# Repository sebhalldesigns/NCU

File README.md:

# NCU
NCU (Network Control Unit)

## Main Connector Pinout

GND
12V

CAN0_L
CAN0_H
CAN1_L
CAN1_H

ETH_TXP
ETH_TXM
ETH_RXP
ETH_RXM

USB_VBUS
USB_DP
USB_DM
GND

AN_5V
AN_GND
AIN_0
AIN_1
AIN_2
AIN_3
AIN_4
AIN_5
AIN_6
AIN_7

HSD_0
HSD_1
HSD_2
HSD_3

LSD_0
LSD_1
LSD_2
LSD_3

TOTAL:
30

## Sheets

Root/
    CONN_A - OK
    CONN_B - OK
    PWR/ - OK
        PWR_LV_5V - OK
        PWR_3V3 - OK
        PWR_A5V - OK
        PWR_MUX - OK
    PHY_CAN/ - OK
        CAN_BUS (x2) - OK
    PHY_ETH - OK
    DRIVES/ - OK
        LSD (x2) - OK
        HSD (x2) - OK
    INPUTS/ - OK
        INPUT_5V (x4) - OK
        INPUT_20V (x5) - OK
    GPIO/ - OK
        INPUT_3V3 (x4) - OK
    CARD_SD - OK
    CARD_SIM - OK
    MOD_WLAN - BAD
    MOD_PCIE - BAD
    MCU - BAD

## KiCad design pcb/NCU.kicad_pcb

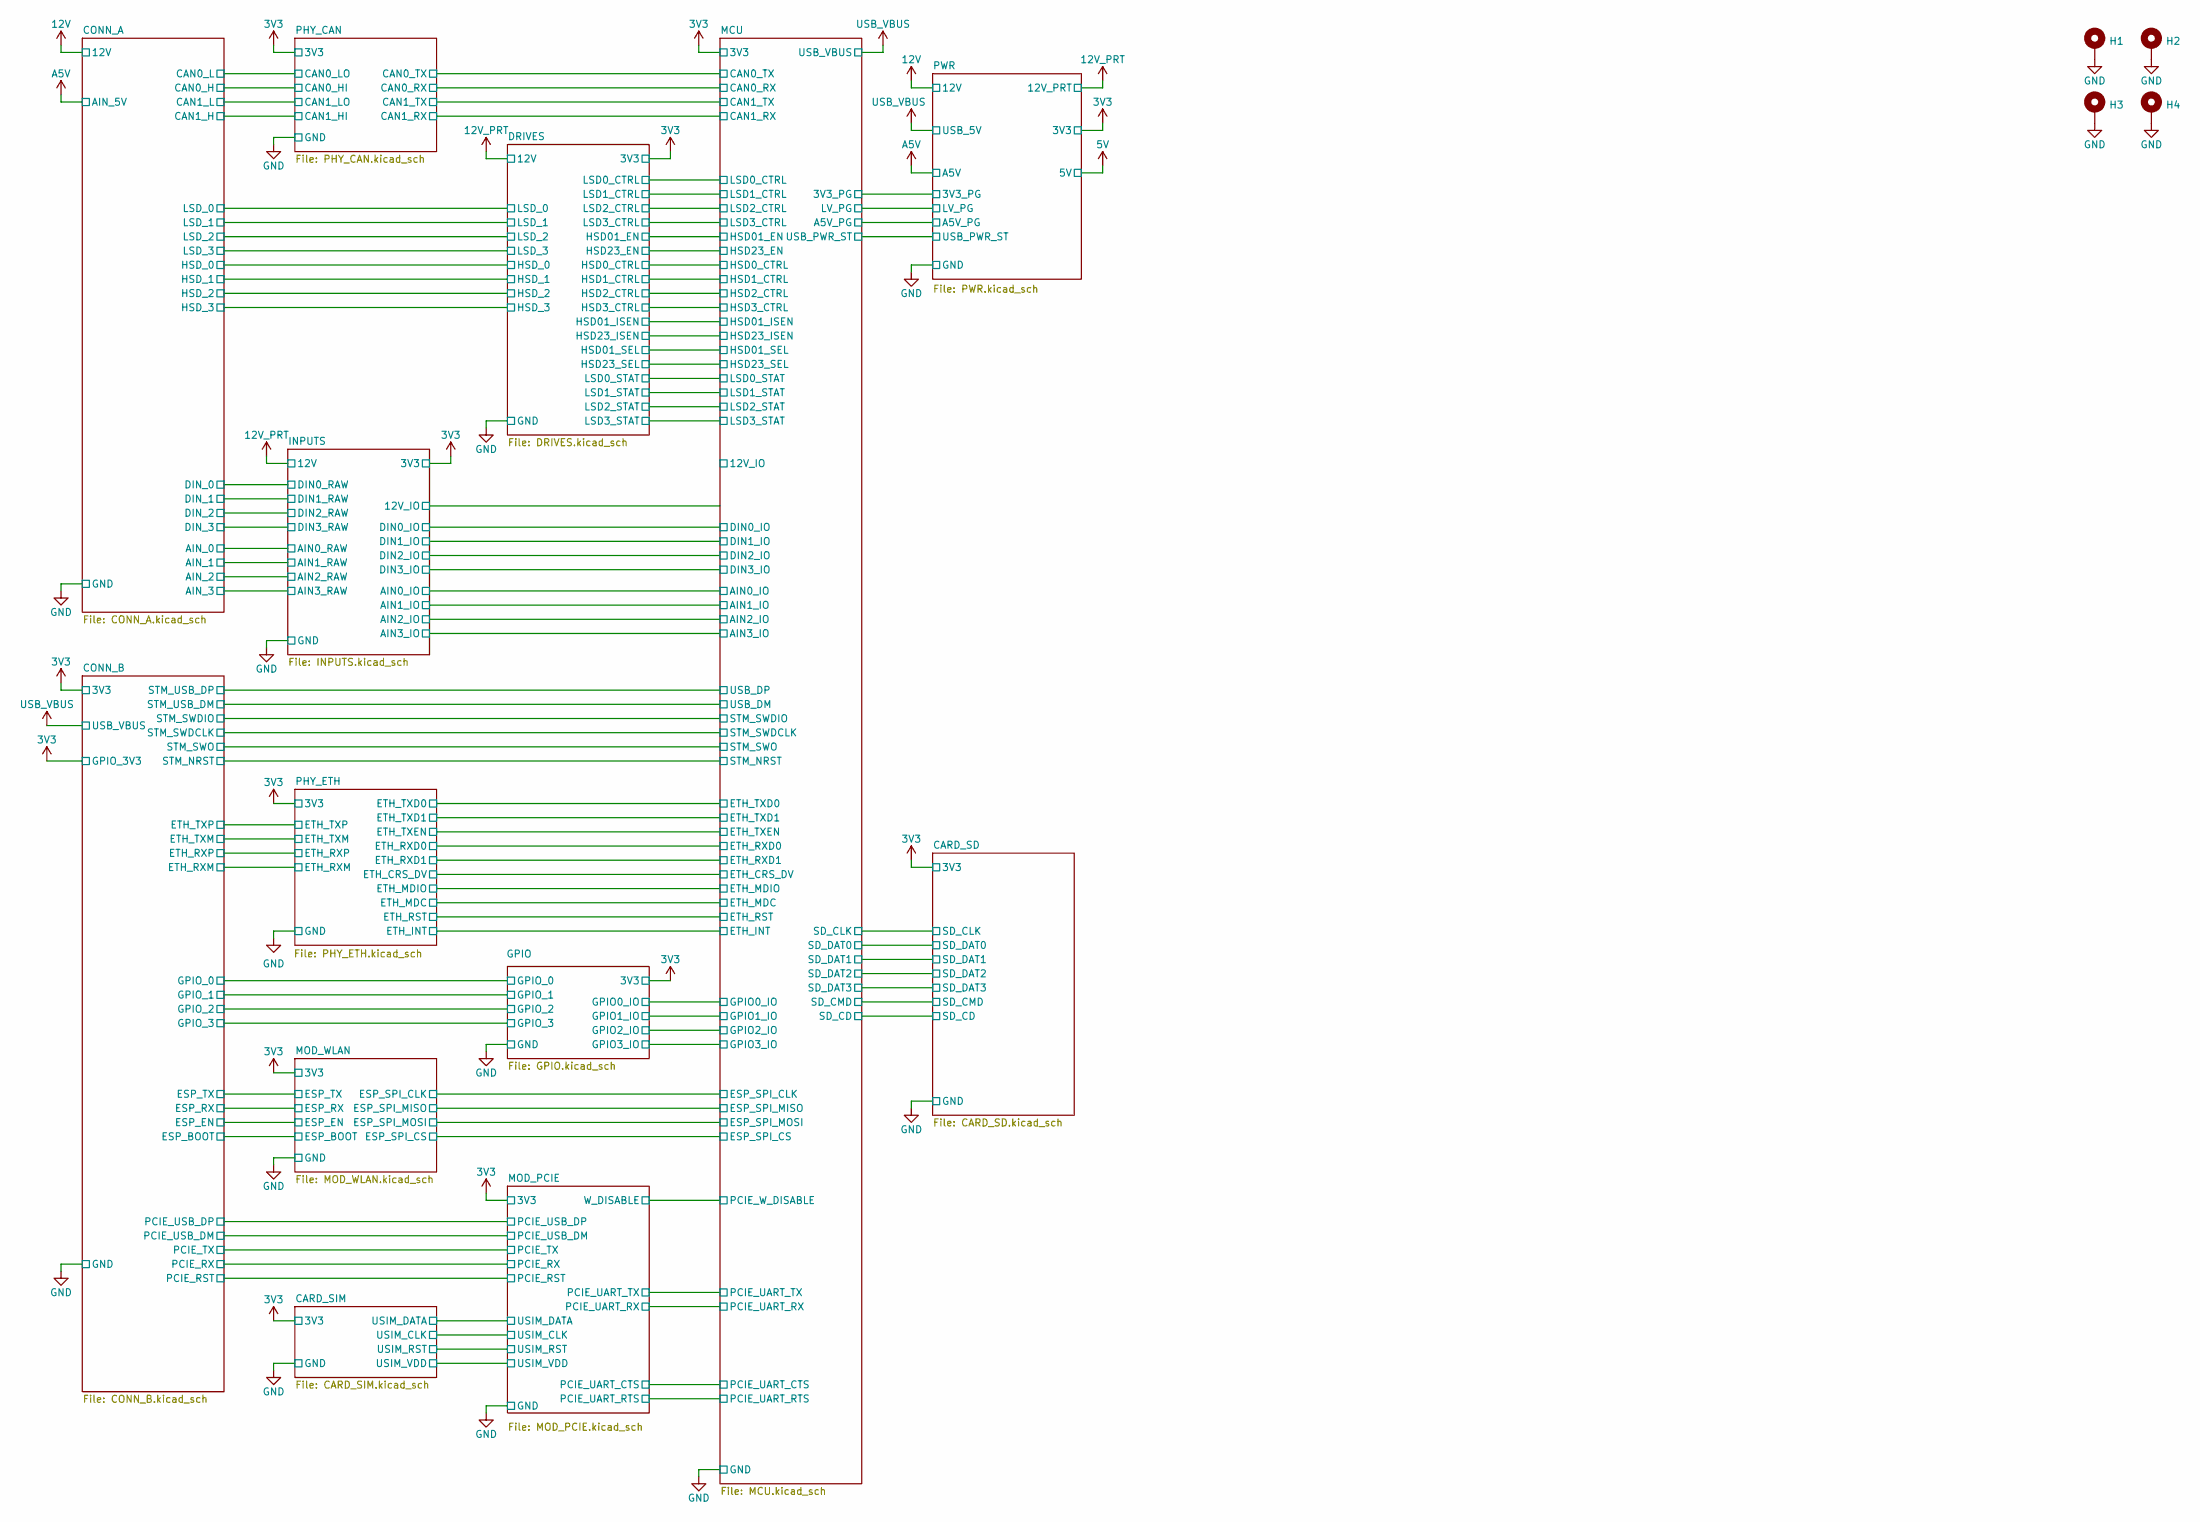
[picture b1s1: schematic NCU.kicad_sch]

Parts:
H1, H2, H3, H4: MountingHole; MountingHole_3.2mm_M3_Pad

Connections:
GND: H1.1, H2.1, H3.1, H4.1; also elsewhere on the board

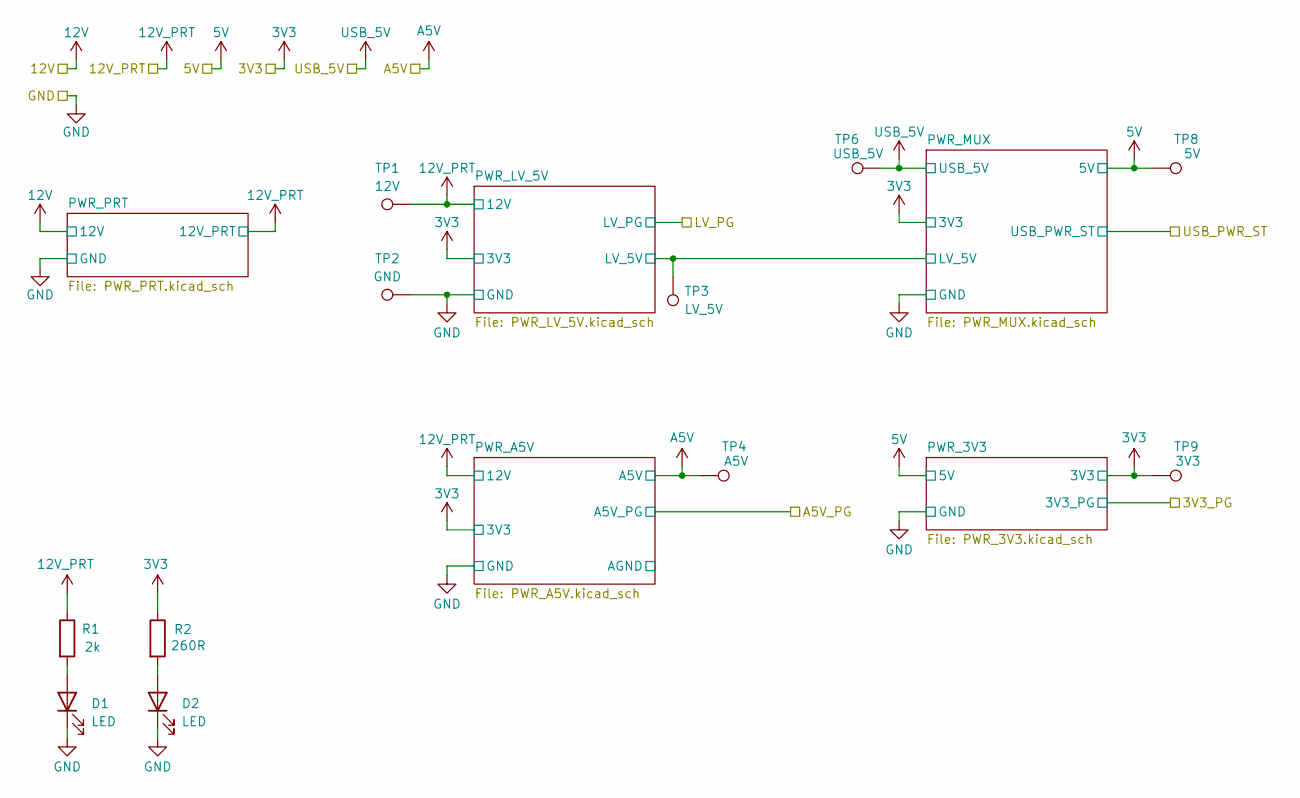
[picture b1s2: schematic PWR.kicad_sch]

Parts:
D1, D2: LED; LED_0603_1608Metric_Pad1.05x0.95mm_HandSolder
R1: 2k; R_0603_1608Metric_Pad0.98x0.95mm_HandSolder
R2: 260R; R_0603_1608Metric_Pad0.98x0.95mm_HandSolder
TP1: 12V; TestPoint_THTPad_D2.0mm_Drill1.0mm
TP2: GND; TestPoint_THTPad_D2.0mm_Drill1.0mm
TP3: LV_5V; TestPoint_THTPad_D2.0mm_Drill1.0mm
TP4: A5V; TestPoint_THTPad_D2.0mm_Drill1.0mm
TP6: USB_5V; TestPoint_THTPad_D2.0mm_Drill1.0mm
TP8: 5V; TestPoint_THTPad_D2.0mm_Drill1.0mm
TP9: 3V3; TestPoint_THTPad_D2.0mm_Drill1.0mm

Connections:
3V3: R2.1, TP9.1; also elsewhere on the board
5V: TP8.1; also elsewhere on the board
12V_PRT: R1.1, TP1.1; also elsewhere on the board
A5V: TP4.1; also elsewhere on the board
GND: D1.1 (K), D2.1 (K), TP2.1; also elsewhere on the board
LV_5V: TP3.1; also elsewhere on the board
unnamed: D1.2 (A), R1.2
unnamed: D2.2 (A), R2.2
USB_VBUS: TP6.1; also elsewhere on the board

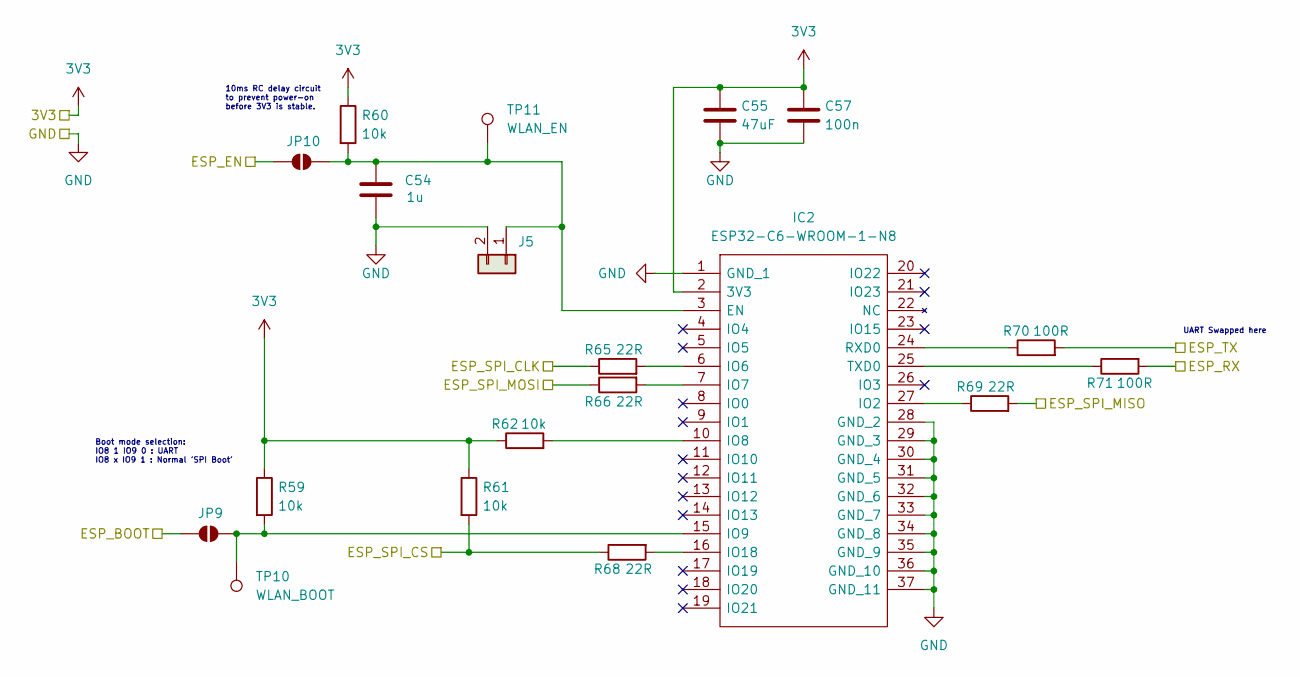
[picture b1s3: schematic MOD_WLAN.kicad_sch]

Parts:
C54: 1u; C_0603_1608Metric_Pad1.08x0.95mm_HandSolder
C55: 47uF; C_0603_1608Metric_Pad1.08x0.95mm_HandSolder
C57: 100n; C_0603_1608Metric_Pad1.08x0.95mm_HandSolder
IC2: ESP32-C6-WROOM-1-N8; ESP32C6WROOM1N8; Mouser Part Number 356-ESP32C6WROOM1N8
J5: Conn_01x02; PinHeader_1x02_P2.54mm_Vertical
JP9, JP10: SolderJumper_2_Open; SolderJumper-2_P1.3mm_Open_RoundedPad1.0x1.5mm
R59, R60, R61, R62: 10k; R_0603_1608Metric_Pad0.98x0.95mm_HandSolder
R65, R66, R68, R69: 22R; R_0603_1608Metric_Pad0.98x0.95mm_HandSolder
R70, R71: 100R; R_0603_1608Metric_Pad0.98x0.95mm_HandSolder
TP10: WLAN_BOOT; TestPoint_THTPad_D2.0mm_Drill1.0mm
TP11: WLAN_EN; TestPoint_THTPad_D2.0mm_Drill1.0mm

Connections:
3V3: C55.1, C57.1, IC2.2 (3V3), R59.1, R60.1, R61.1, R62.1; also elsewhere on the board
/CONN_B/ESP_BOOT: JP9.1 (A); also elsewhere on the board
/CONN_B/ESP_EN: JP10.1 (A); also elsewhere on the board
/CONN_B/ESP_RX: R71.2; also elsewhere on the board
/CONN_B/ESP_TX: R70.2; also elsewhere on the board
/MCU/ESP_SPI_CLK: R65.1; also elsewhere on the board
/MCU/ESP_SPI_CS: R61.2, R68.1; also elsewhere on the board
/MCU/ESP_SPI_MISO: R69.2; also elsewhere on the board
/MCU/ESP_SPI_MOSI: R66.1; also elsewhere on the board
GND: C54.2, C55.2, C57.2, IC2.1 (GND_1), IC2.28 (GND_2), IC2.29 (GND_3), IC2.30 (GND_4), IC2.31 (GND_5), IC2.32 (GND_6), IC2.33 (GND_7), IC2.34 (GND_8), IC2.35 (GND_9), IC2.36 (GND_10), IC2.37 (GND_11), J5.2; also elsewhere on the board
unnamed: C54.1, IC2.3 (EN), J5.1, JP10.2 (B), R60.2, TP11.1
unnamed: IC2.27 (IO2), R69.1
unnamed: IC2.6 (IO6), R65.2
unnamed: IC2.7 (IO7), R66.2
unnamed: IC2.10 (IO8), R62.2
unnamed: IC2.15 (IO9), JP9.2 (B), R59.2, TP10.1
unnamed: IC2.16 (IO18), R68.2
unnamed: IC2.24 (RXD0), R70.1
unnamed: IC2.25 (TXD0), R71.1

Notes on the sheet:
Boot mode selection: IO8 1 IO9 0 : UART IO8 x IO9 1 : Normal 'SPI Boot'
10ms RC delay circuit to prevent power-on before 3V3 is stable.
UART Swapped here

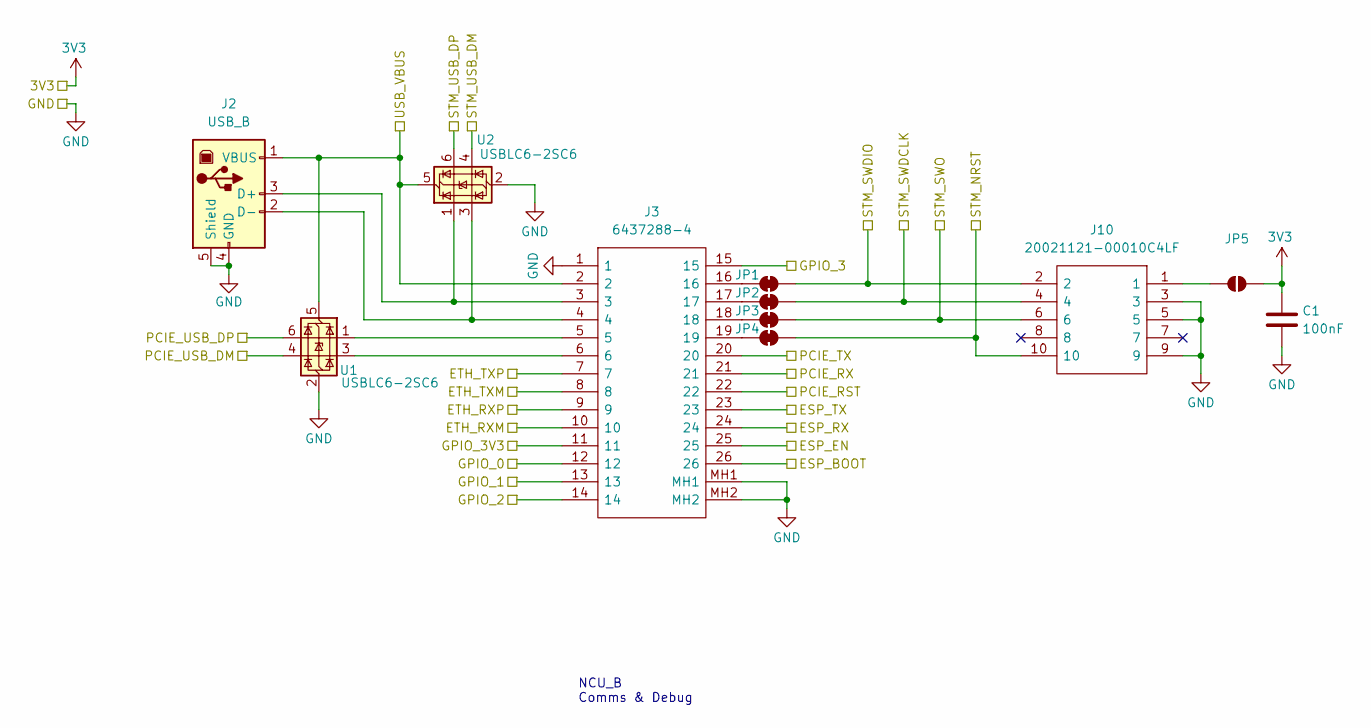
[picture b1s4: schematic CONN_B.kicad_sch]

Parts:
C1: 100nF; C_0603_1608Metric_Pad1.08x0.95mm_HandSolder
J2: USB_B; USB_B_OST_USB-B1HSxx_Horizontal
J3: 6437288-4; 64372884; Mouser Part Number 571-6437288-4
J10: 20021121-00010C4LF; 2002112100010C4LF; Mouser Part Number 649-202112100010C4LF
JP1, JP2, JP3, JP4: SolderJumper_2_Bridged; SolderJumper-2_P1.3mm_Bridged_RoundedPad1.0x1.5mm
JP5: SolderJumper_2_Open; SolderJumper-2_P1.3mm_Open_RoundedPad1.0x1.5mm
U1, U2: USBLC6-2SC6; SOT-23-6

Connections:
3V3: C1.1, J3.11, JP5.2 (B); also elsewhere on the board
/CONN_B/ESP_BOOT: J3.26; also elsewhere on the board
/CONN_B/ESP_EN: J3.25; also elsewhere on the board
/CONN_B/ESP_RX: J3.24; also elsewhere on the board
/CONN_B/ESP_TX: J3.23; also elsewhere on the board
/CONN_B/ETH_RXM: J3.10; also elsewhere on the board
/CONN_B/ETH_RXP: J3.9; also elsewhere on the board
/CONN_B/ETH_TXM: J3.8; also elsewhere on the board
/CONN_B/ETH_TXP: J3.7; also elsewhere on the board
/CONN_B/GPIO_0: J3.12; also elsewhere on the board
/CONN_B/GPIO_1: J3.13; also elsewhere on the board
/CONN_B/GPIO_2: J3.14; also elsewhere on the board
/CONN_B/GPIO_3: J3.15; also elsewhere on the board
/CONN_B/PCIE_RST: J3.22; also elsewhere on the board
/CONN_B/PCIE_RX: J3.21; also elsewhere on the board
/CONN_B/PCIE_TX: J3.20; also elsewhere on the board
/CONN_B/PCIE_USB_DM: U1.4 (I/O2); also elsewhere on the board
/CONN_B/PCIE_USB_DP: U1.6 (I/O1); also elsewhere on the board
/CONN_B/STM_SWDCLK: J10.4, JP2.2 (B); also elsewhere on the board
/CONN_B/STM_SWDIO: J10.2, JP1.2 (B); also elsewhere on the board
/CONN_B/STM_SWO: J10.6, JP3.2 (B); also elsewhere on the board
/CONN_B/STM_USB_DM: U2.4 (I/O2); also elsewhere on the board
/CONN_B/STM_USB_DP: U2.6 (I/O1); also elsewhere on the board
/MCU/STM_NRST: J10.10, JP4.2 (B); also elsewhere on the board
GND: C1.2, J2.4 (GND), J2.5 (Shield), J3.1, J3.MH1, J3.MH2, J10.3, J10.5, J10.9, U1.2 (GND), U2.2 (GND); also elsewhere on the board
unnamed: J2.3 (D+), J3.3, U2.1 (I/O1)
unnamed: J2.2 (D-), J3.4, U2.3 (I/O2)
unnamed: J3.5, U1.1 (I/O1)
unnamed: J3.6, U1.3 (I/O2)
unnamed: J3.16, JP1.1 (A)
unnamed: J3.17, JP2.1 (A)
unnamed: J3.18, JP3.1 (A)
unnamed: J3.19, JP4.1 (A)
unnamed: J10.1, JP5.1 (A)
USB_VBUS: J2.1 (VBUS), J3.2, U1.5 (VBUS), U2.5 (VBUS); also elsewhere on the board

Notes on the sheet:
NCU_B Comms & Debug

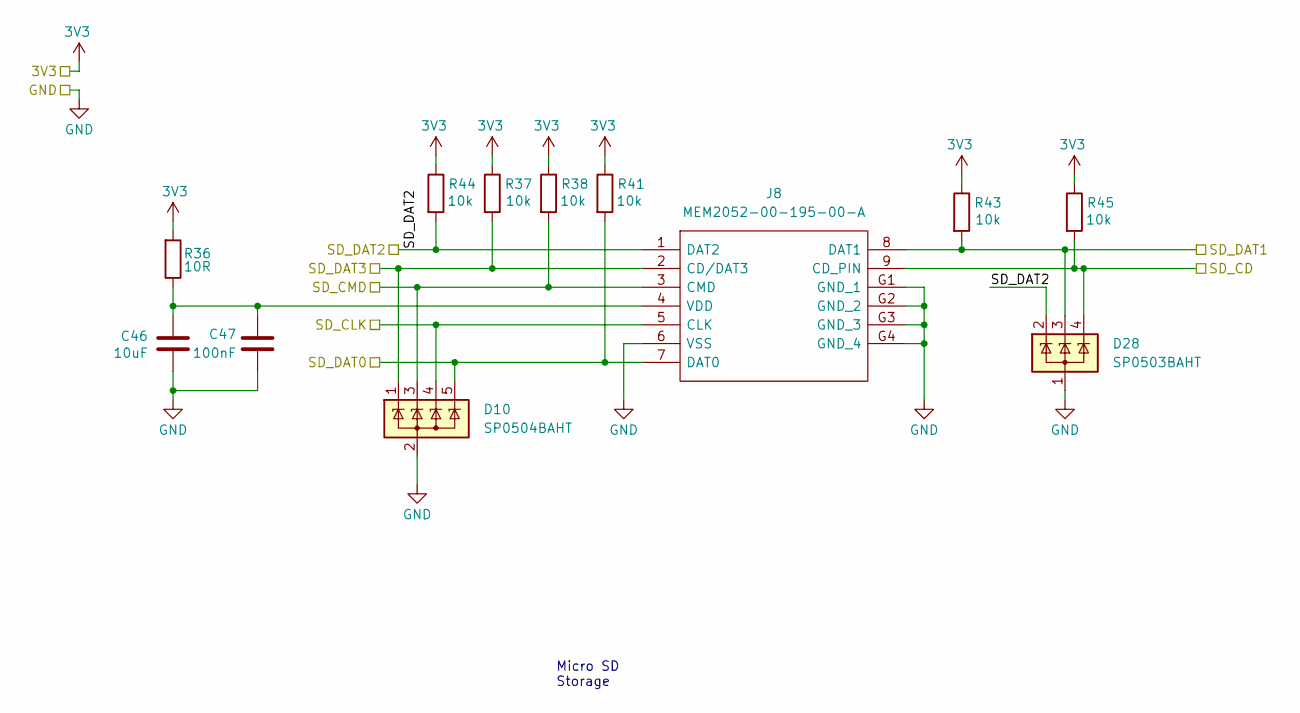
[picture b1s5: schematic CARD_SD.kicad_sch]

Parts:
C46: 10uF; C_0603_1608Metric_Pad1.08x0.95mm_HandSolder
C47: 100nF; C_0603_1608Metric_Pad1.08x0.95mm_HandSolder
D10: SP0504BAHT; SOT-23-5
D28: SP0503BAHT; SOT-143
J8: MEM2052-00-195-00-A; MEM20520019500A; Mouser Part Number 640-MEM20520019500A
R36: 10R; R_0603_1608Metric_Pad0.98x0.95mm_HandSolder
R37, R38, R41, R43, R44, R45: 10k; R_0603_1608Metric_Pad0.98x0.95mm_HandSolder

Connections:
3V3: R36.2, R37.1, R38.1, R41.1, R43.1, R44.1, R45.1; also elsewhere on the board
/CARD_SD/SD_CD: D28.4 (K), J8.9 (CD_PIN), R45.2; also elsewhere on the board
/CARD_SD/SD_CLK: D10.4 (K), J8.5 (CLK); also elsewhere on the board
/CARD_SD/SD_CMD: D10.3 (K), J8.3 (CMD), R38.2; also elsewhere on the board
/CARD_SD/SD_DAT0: D10.5 (K), J8.7 (DAT0), R41.2; also elsewhere on the board
/CARD_SD/SD_DAT1: D28.3 (K), J8.8 (DAT1), R43.2; also elsewhere on the board
/CARD_SD/SD_DAT2: D28.2 (K), J8.1 (DAT2), R44.2; also elsewhere on the board
/CARD_SD/SD_DAT3: D10.1 (K), J8.2 (CD/DAT3), R37.2; also elsewhere on the board
GND: C46.2, C47.2, D10.2 (A), D28.1 (A), J8.6 (VSS), J8.G1 (GND_1), J8.G2 (GND_2), J8.G3 (GND_3), J8.G4 (GND_4); also elsewhere on the board
unnamed: C46.1, C47.1, J8.4 (VDD), R36.1

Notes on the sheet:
Micro SD Storage

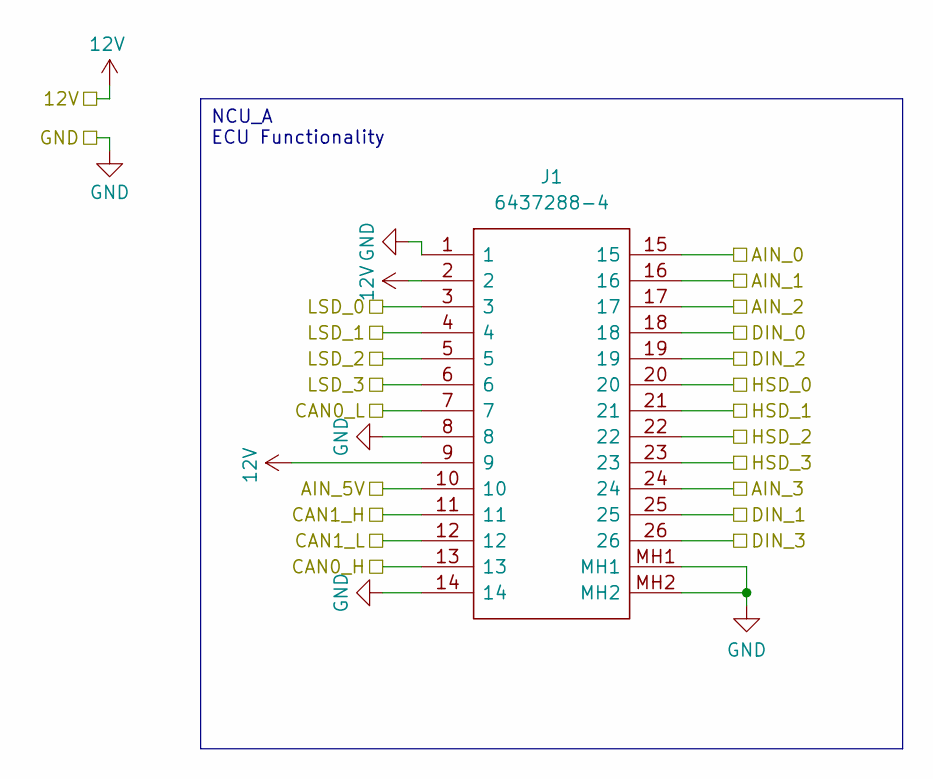
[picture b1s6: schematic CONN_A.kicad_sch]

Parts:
J1: 6437288-4; 64372884; Mouser Part Number 571-6437288-4

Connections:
12V: J1.2, J1.9; also elsewhere on the board
/CONN_A/AIN_0: J1.15; also elsewhere on the board
/CONN_A/AIN_1: J1.16; also elsewhere on the board
/CONN_A/AIN_2: J1.17; also elsewhere on the board
/CONN_A/AIN_3: J1.24; also elsewhere on the board
/CONN_A/CAN0_H: J1.13; also elsewhere on the board
/CONN_A/CAN0_L: J1.7; also elsewhere on the board
/CONN_A/CAN1_H: J1.11; also elsewhere on the board
/CONN_A/CAN1_L: J1.12; also elsewhere on the board
/CONN_A/DIN_0: J1.18; also elsewhere on the board
/CONN_A/DIN_1: J1.25; also elsewhere on the board
/CONN_A/DIN_2: J1.19; also elsewhere on the board
/CONN_A/DIN_3: J1.26; also elsewhere on the board
/CONN_A/HSD_0: J1.20; also elsewhere on the board
/CONN_A/HSD_1: J1.21; also elsewhere on the board
/CONN_A/HSD_2: J1.22; also elsewhere on the board
/CONN_A/HSD_3: J1.23; also elsewhere on the board
/CONN_A/LSD_0: J1.3; also elsewhere on the board
/CONN_A/LSD_1: J1.4; also elsewhere on the board
/CONN_A/LSD_2: J1.5; also elsewhere on the board
/CONN_A/LSD_3: J1.6; also elsewhere on the board
A5V: J1.10; also elsewhere on the board
GND: J1.1, J1.8, J1.14, J1.MH1, J1.MH2; also elsewhere on the board

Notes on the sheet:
NCU_A ECU Functionality

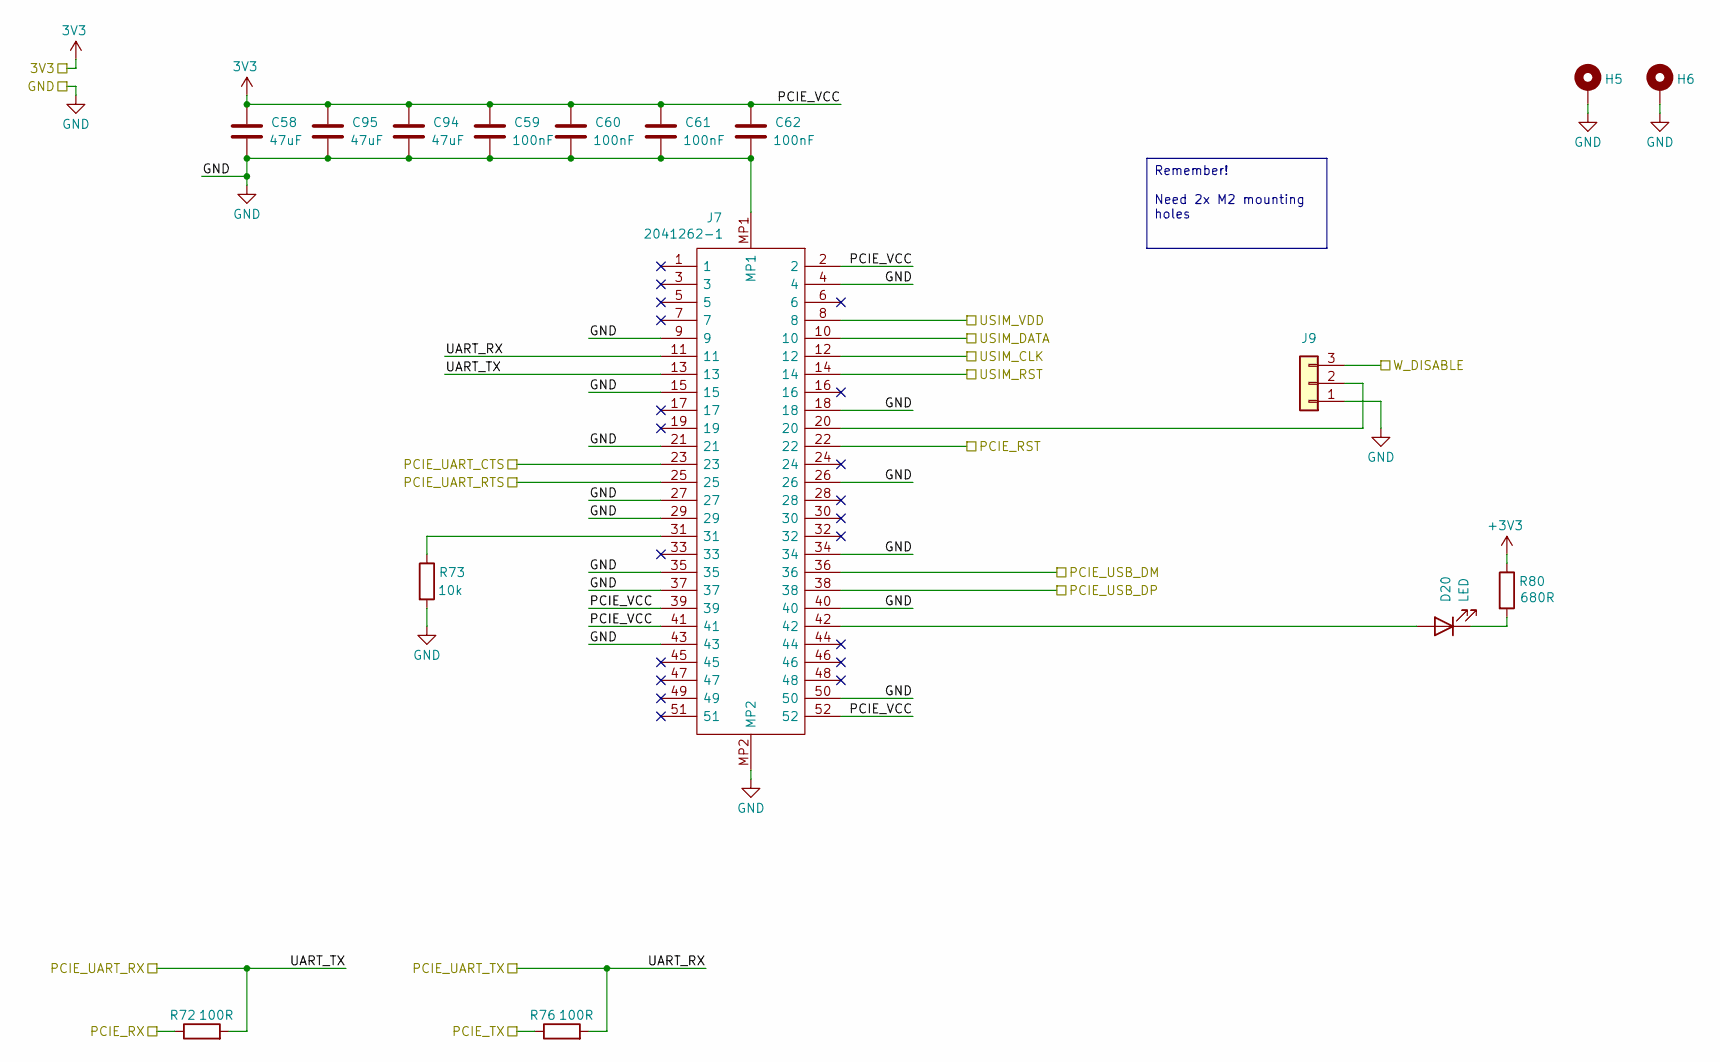
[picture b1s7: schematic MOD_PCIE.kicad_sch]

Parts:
C58, C94, C95: 47uF; C_0603_1608Metric_Pad1.08x0.95mm_HandSolder
C59, C60, C61, C62: 100nF; C_0603_1608Metric_Pad1.08x0.95mm_HandSolder
D20: LED; LED_0603_1608Metric_Pad1.05x0.95mm_HandSolder
H5, H6: MountingHole_Pad; MountingHole_2.7mm_M2.5_Pad
J7: 2041262-1; 20412621; Mouser Part Number 571-2041262-1
J9: Conn_01x03; PinHeader_1x03_P2.54mm_Vertical
R72, R76: 100R; R_0603_1608Metric_Pad0.98x0.95mm_HandSolder
R73: 10k; R_0603_1608Metric_Pad0.98x0.95mm_HandSolder
R80: 680R; R_0603_1608Metric_Pad0.98x0.95mm_HandSolder

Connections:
3V3: C58.1, C59.1, C60.1, C61.1, C62.1, C94.1, C95.1, J7.2, J7.39, J7.41, J7.52; also elsewhere on the board
+3V3: R80.1
/CARD_SIM/USIM_CLK: J7.12; also elsewhere on the board
/CARD_SIM/USIM_DATA: J7.10; also elsewhere on the board
/CARD_SIM/USIM_RST: J7.14; also elsewhere on the board
/CARD_SIM/USIM_VDD: J7.8; also elsewhere on the board
/CONN_B/PCIE_RST: J7.22; also elsewhere on the board
/CONN_B/PCIE_RX: R72.1; also elsewhere on the board
/CONN_B/PCIE_TX: R76.1; also elsewhere on the board
/CONN_B/PCIE_USB_DM: J7.36; also elsewhere on the board
/CONN_B/PCIE_USB_DP: J7.38; also elsewhere on the board
/MCU/PCIE_UART_CTS: J7.23; also elsewhere on the board
/MCU/PCIE_UART_RTS: J7.25; also elsewhere on the board
/MCU/PCIE_W_DISABLE: J9.3; also elsewhere on the board
/MOD_PCIE/UART_RX: J7.11, R76.2; also elsewhere on the board
/MOD_PCIE/UART_TX: J7.13, R72.2; also elsewhere on the board
GND: C58.2, C59.2, C60.2, C61.2, C62.2, C94.2, C95.2, H5.1, H6.1, J7.4, J7.9, J7.15, J7.18, J7.21, J7.26, J7.27, J7.29, J7.34, J7.35, J7.37, J7.40, J7.43, J7.50, J7.MP1, J7.MP2, J9.1, R73.2; also elsewhere on the board
unnamed: D20.2 (A), J7.42
unnamed: D20.1 (K), R80.2
unnamed: J7.31, R73.1
unnamed: J7.20, J9.2

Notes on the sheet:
Remember! Need 2x M2 mounting holes

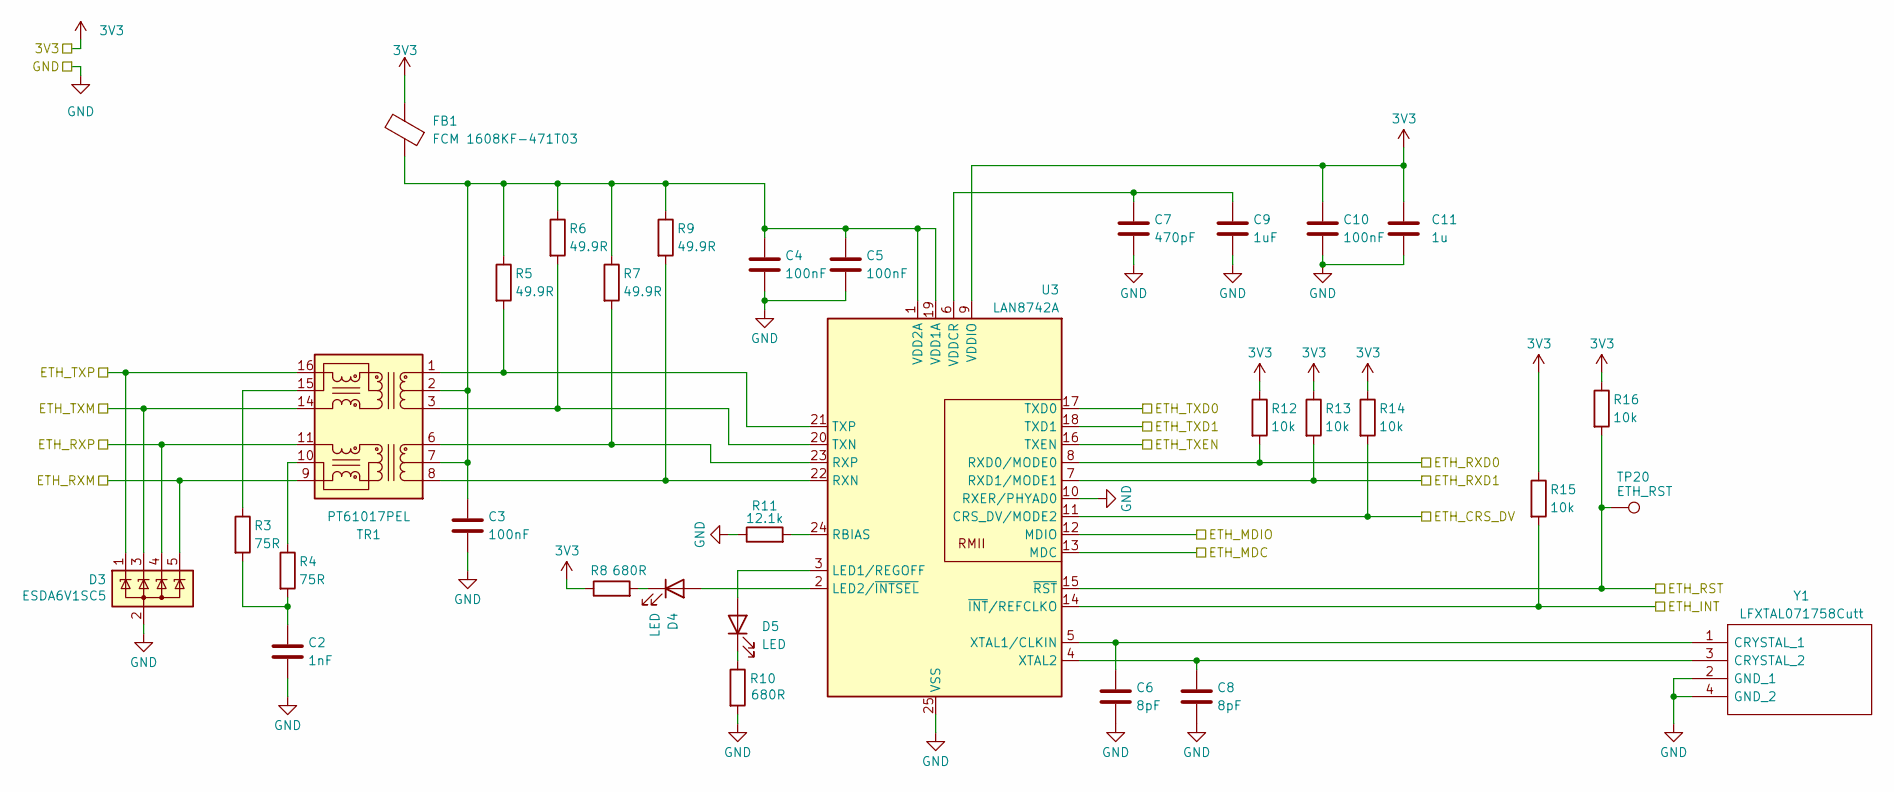
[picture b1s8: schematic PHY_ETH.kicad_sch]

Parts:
C2: 1nF; C_0603_1608Metric_Pad1.08x0.95mm_HandSolder
C3, C4, C5, C10: 100nF; C_0603_1608Metric_Pad1.08x0.95mm_HandSolder
C6, C8: 8pF; C_0603_1608Metric_Pad1.08x0.95mm_HandSolder
C7: 470pF; C_0603_1608Metric_Pad1.08x0.95mm_HandSolder
C9: 1uF; C_0603_1608Metric_Pad1.08x0.95mm_HandSolder
C11: 1u; C_0603_1608Metric_Pad1.08x0.95mm_HandSolder
D3: ESDA6V1SC5; SOT-23-5
D4, D5: LED; LED_0603_1608Metric_Pad1.05x0.95mm_HandSolder
FB1: FCM 1608KF-471T03; L_0603_1608Metric_Pad1.05x0.95mm_HandSolder
R3, R4: 75R; R_0603_1608Metric_Pad0.98x0.95mm_HandSolder
R5, R6, R7, R9: 49.9R; R_0603_1608Metric_Pad0.98x0.95mm_HandSolder
R8, R10: 680R; R_0603_1608Metric_Pad0.98x0.95mm_HandSolder
R11: 12.1k; R_0603_1608Metric_Pad0.98x0.95mm_HandSolder
R12, R13, R14, R15, R16: 10k; R_0603_1608Metric_Pad0.98x0.95mm_HandSolder
TP20: ETH_RST; TestPoint_THTPad_D2.0mm_Drill1.0mm
TR1: PT61017PEL; Transformer_Ethernet_Bourns_PT61017PEL
U3: LAN8742A; VQFN-24-1EP_4x4mm_P0.5mm_EP2.5x2.5mm_ThermalVias
Y1: LFXTAL071758Cutt; Mouser Part Number 449-LFXTAL071758CUTT

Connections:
3V3: C10.1, C11.1, FB1.2, R8.1, R12.1, R13.1, R14.1, R15.1, R16.1, U3.9 (VDDIO); also elsewhere on the board
/CONN_B/ETH_RXM: D3.5 (K), TR1.9 (RX-); also elsewhere on the board
/CONN_B/ETH_RXP: D3.4 (K), TR1.11 (RX+); also elsewhere on the board
/CONN_B/ETH_TXM: D3.3 (K), TR1.14 (TX-); also elsewhere on the board
/CONN_B/ETH_TXP: D3.1 (K), TR1.16 (TX+); also elsewhere on the board
/MCU/ETH_CRS_DV: R14.2, U3.11 (CRS_DV/MODE2); also elsewhere on the board
/MCU/ETH_INT: R15.2, U3.14 (~INT/REFCLKO); also elsewhere on the board
/MCU/ETH_MDC: U3.13 (MDC); also elsewhere on the board
/MCU/ETH_MDIO: U3.12 (MDIO); also elsewhere on the board
/MCU/ETH_RST: R16.2, TP20.1, U3.15 (~RST); also elsewhere on the board
/MCU/ETH_RXD0: R12.2, U3.8 (RXD0/MODE0); also elsewhere on the board
/MCU/ETH_RXD1: R13.2, U3.7 (RXD1/MODE1); also elsewhere on the board
/MCU/ETH_TXD0: U3.17 (TXD0); also elsewhere on the board
/MCU/ETH_TXD1: U3.18 (TXD1); also elsewhere on the board
/MCU/ETH_TXEN: U3.16 (TXEN); also elsewhere on the board
GND: C2.2, C3.2, C4.2, C5.2, C6.2, C7.2, C8.2, C9.2, C10.2, C11.2, D3.2 (A), R10.2, R11.1, U3.10 (RXER/PHYAD0), U3.25 (VSS), Y1.2 (GND_1), Y1.4 (GND_2); also elsewhere on the board
unnamed: C2.1, R3.2, R4.2
unnamed: D4.2 (A), U3.2 (LED2/~INTSEL)
unnamed: D4.1 (K), R8.2
unnamed: D5.2 (A), U3.3 (LED1/REGOFF)
unnamed: D5.1 (K), R10.1
unnamed: C3.1, C4.1, C5.1, FB1.1, R5.1, R6.1, R7.1, R9.1, TR1.2 (C_TD), TR1.7 (C_RD), U3.1 (VDD2A), U3.19 (VDD1A)
unnamed: R4.1, TR1.10 (C_RX)
unnamed: R3.1, TR1.15 (C_TX)
unnamed: R7.2, TR1.6 (RD+), U3.23 (RXP)
unnamed: R9.2, TR1.8 (RD-), U3.22 (RXN)
unnamed: R5.2, TR1.1 (TD+), U3.21 (TXP)
unnamed: R6.2, TR1.3 (TD-), U3.20 (TXN)
unnamed: R11.2, U3.24 (RBIAS)
unnamed: C7.1, C9.1, U3.6 (VDDCR)
unnamed: C6.1, U3.5 (XTAL1/CLKIN), Y1.1 (CRYSTAL_1)
unnamed: C8.1, U3.4 (XTAL2), Y1.3 (CRYSTAL_2)

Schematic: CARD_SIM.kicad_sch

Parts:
C49: 100n; C_0603_1608Metric_Pad1.08x0.95mm_HandSolder
D13: SP0503BAHT; SOT-143
J6: SF56K006VBAR2000; Mouser Part Number 656-SF56K006VBAR2000

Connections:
/CARD_SIM/USIM_CLK: D13.3 (K), J6.C3 (CLK); also elsewhere on the board
/CARD_SIM/USIM_DATA: D13.4 (K), J6.C7 (I/O); also elsewhere on the board
/CARD_SIM/USIM_RST: D13.2 (K), J6.C2 (RST); also elsewhere on the board
/CARD_SIM/USIM_VDD: C49.1, J6.C1 (VCC); also elsewhere on the board
GND: C49.2, D13.1 (A), J6.C5 (GND_1), J6.D1 (DUMMY_1), J6.D2 (DUMMY_2), J6.D3 (DUMMY_3), J6.D4 (DUMMY_4), J6.D5 (DUMMY_5), J6.D6 (DUMMY_6), J6.DSW1 (GND_2), J6.DSW2, J6.G1 (GND1), J6.G2 (GND2), J6.G3 (GND3), J6.G4 (GND4), J6.G5 (GND5), J6.G6 (GND6); also elsewhere on the board

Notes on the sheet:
Mini SIM Cellular
